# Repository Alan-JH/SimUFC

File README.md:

# SimUFC
UFC design for DCS, based on the F-18C Hornet

Display panels originally designed by [OpenHornet](https://github.com/jrsteensen/OpenHornet) and remixed to use .1" headers and multiplexed digits instead of multiplexed half digits.

Displays driven by Holtek HT1632Cs. Board is designed to take Cherry style key switches. I am using Kailh Box Jades, hence the SMD LEDs.

Main assembly is two large PCBs stacked, with the back PCB housing the LED drivers and microcontroller. It is designed to also take a shift register PCB of one of my older designs. It will be replaced later on.

Microcontroller is an STM32 Bluepill.

[![CC BY-NC-SA 4.0][cc-by-nc-sa-shield]][cc-by-nc-sa]

This work is licensed under a
[Creative Commons Attribution-NonCommercial-ShareAlike 4.0 International License][cc-by-nc-sa].

[![CC BY-NC-SA 4.0][cc-by-nc-sa-image]][cc-by-nc-sa]

[cc-by-nc-sa]: http://creativecommons.org/licenses/by-nc-sa/4.0/
[cc-by-nc-sa-image]: https://licensebuttons.net/l/by-nc-sa/4.0/88x31.png
[cc-by-nc-sa-shield]: https://img.shields.io/badge/License-CC%20BY--NC--SA%204.0-lightgrey.svg

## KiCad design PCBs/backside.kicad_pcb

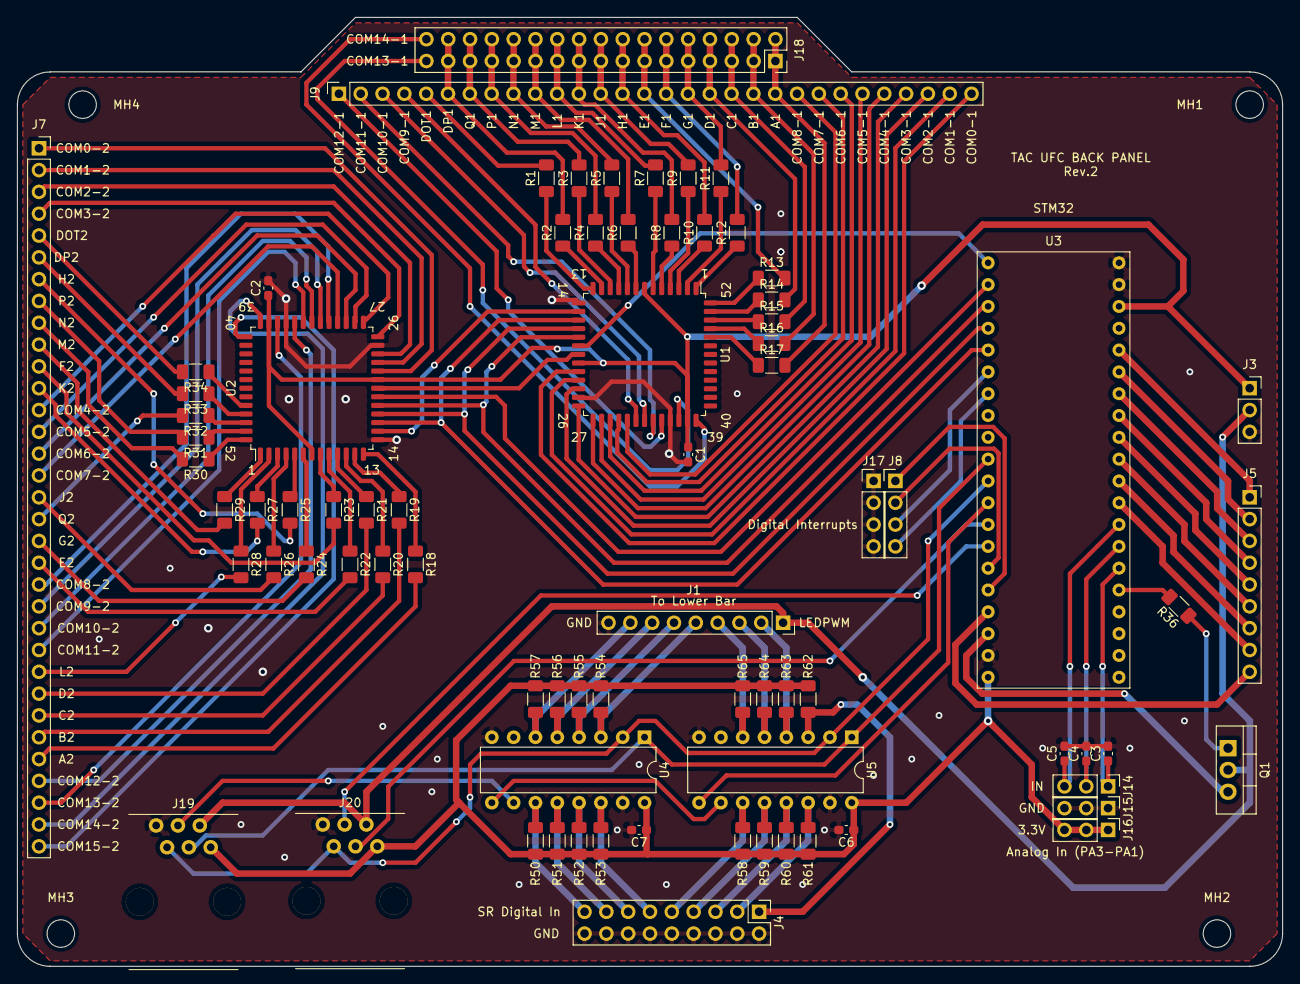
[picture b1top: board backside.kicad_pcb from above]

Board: 2 copper layers, 147.3 x 110.5 mm, 82 parts (0 on the bottom side), 151 nets.

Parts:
C1, C2, C3, C4, C5, C6, C7: .1uF; C_0603_1608Metric_Pad1.08x0.95mm_HandSolder
J1: 9Pin; PinSocket_1x09_P2.54mm_Vertical
J3: Power; PinSocket_1x03_P2.54mm_Vertical
J4: Conn_02x09_Odd_Even; PinHeader_2x09_P2.54mm_Vertical
J5: Matrix; PinSocket_1x09_P2.54mm_Vertical
J7: Driver output 2; PinSocket_1x33_P2.54mm_Vertical
J8, J17: Conn_01x04_Male; PinHeader_1x04_P2.54mm_Vertical
J9: Conn_01x30_Male; PinSocket_1x30_P2.54mm_Vertical
J14, J15, J16: Conn_01x03_Male; PinHeader_1x03_P2.54mm_Vertical
J18: Conn_02x17_Odd_Even; PinSocket_2x17_P2.54mm_Vertical
J19, J20: RJ12; SS-6466-NF
MH1, MH2, MH3, MH4: MountingHole_3.2mm_M3
Q1: IPP120P04P4L03; TO-220-3_Vertical
R1, R2, R3, R4, R5, R6, R7, R8, R9, R10, R11, R12, R13, R14, R15, R16, R17, R18, R19, R20, R21, R22, R23, R24, R25, R26, R27, R28, R29, R30, R31, R32, R33, R34: 510R; R_1206_3216Metric_Pad1.30x1.75mm_HandSolder
R36: 100R; R_1206_3216Metric_Pad1.30x1.75mm_HandSolder
R50, R51, R52, R53, R54, R55, R56, R57, R58, R59, R60, R61, R62, R63, R64, R65: 10K; R_1206_3216Metric_Pad1.30x1.75mm_HandSolder
U1, U2: HT1632C-52LQFP; LQFP-52_14x14mm_P1mm
U3: STM32F103C8T6; Bluepill
U4, U5: 74HC165; DIP-16_W7.62mm

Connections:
/3.3V: C1.1, C2.1, C6.1, C7.1, J3.1, J16.1, J16.2, J16.3, J19.6, J20.6, R50.2, R51.2, R52.2, R53.2, R54.2, R55.2, R56.2, R57.2, R58.2, R59.2, R60.2, R61.2, R62.2, R63.2, R64.2, R65.2, U1.7, U1.21, U1.38, U2.7, U2.21, U2.38, U3.47, U3.52, U4.16, U5.16
/5V: Q1.3, U3.50
/A1: J9.21, J18.1, J18.2, R17.2
/A2: J7.29, R18.2
/Analog1: C3.1, J14.1, U3.11
/Analog2: C4.1, J14.2, U3.12
/Analog3: C5.1, J14.3, U3.13
/B1: J9.20, J18.3, J18.4, R16.2
/B2: J7.28, R19.2
/C1: J9.19, J18.5, J18.6, R15.2
/C2: J7.27, R20.2
/COL1: J5.4, U3.18
/COL2: J5.3, U3.19
/COL3: J5.2, U3.21
/COL4: J5.1, U3.22
/COM0-1: J9.30, U1.22
/COM0-2: J7.1, U2.22
/COM1-1: J9.29, U1.23
/COM1-2: J7.2, U2.23
/COM2-1: J9.28, U1.24
/COM2-2: J7.3, U2.24
/COM3-1: J9.27, U1.26
/COM3-2: J7.4, U2.26
/COM4-1: J9.26, U1.27
/COM4-2: J7.13, U2.27
/COM5-1: J9.25, U1.28
/COM5-2: J7.14, U2.28
/COM6-1: J9.24, U1.29
/COM6-2: J7.15, U2.29
/COM7-1: J9.23, U1.30
/COM7-2: J7.16, U2.30
/COM8-1: J9.22, U1.31
/COM8-2: J7.21, U2.31
/COM9-1: J9.4, U1.32
/COM9-2: J7.22, U2.32
/COM10-1: J9.3, U1.33
/COM10-2: J7.23, U2.33
/COM11-1: J9.2, U1.34
/COM11-2: J7.24, U2.34
/COM12-1: J9.1, U1.35
/COM12-2: J7.30, U2.35
/COM13-1: J18.33, U1.37
/COM13-2: J7.31, U2.37
/COM14-1: J18.34, U1.39
/COM14-2: J7.32, U2.39
/COM15-2: J7.33, U2.40
/CS1: U1.19, U3.25
/CS2: U2.19, U3.26
/D1: J9.18, J18.7, J18.8, R14.2
/D2: J7.26, R21.2
/DATA: U1.16, U2.16, U3.29
/DIN1: J4.1, R62.1, U5.3
/DIN2: J4.3, R61.1, U5.14
/DIN3: J4.5, R60.1, U5.13
/DIN4: J4.7, R59.1, U5.12
/DIN5: J4.9, R58.1, U5.11
/DIN6: J4.11, R53.1, U4.14
/DIN7: J4.13, R52.1, U4.13
/DIN8: J4.15, R51.1, U4.12
/DIN9: J4.17, R50.1, U4.11
/DOT1: J9.5, R1.2
/DOT2: J7.5, R34.2
/DP1: J9.6, J18.31, J18.32, R2.2
/DP2: J7.6, R33.2
/DSIN: J19.3, U4.10
/DigInt1: J8.1, U3.45
/DigInt2: J8.2, U3.43
/DigInt3: J8.3, U3.30
/DigInt4: J8.4, U3.31
/E1: J9.15, J18.13, J18.14, R13.2
/E2: J7.20, R22.2
/F1: J9.16, J18.11, J18.12, R12.2
/F2: J7.11, R23.2
/G1: J9.17, J18.9, J18.10, R11.2
/G2: J7.19, R24.2
/GND: C1.2, C2.2, C3.2, C4.2, C5.2, C6.2, C7.2, J1.9, J3.3, J4.2, J4.4, J4.6, J4.8, J4.10, J4.12, J4.14, J4.16, J4.18, J15.1, J15.2, J15.3, J17.1, J17.2, J17.3, J17.4, J19.1, J20.1, U1.14, U1.25, U1.36, U2.14, U2.25, U2.36, U3.48, U3.49, U3.51, U4.8, U4.15, U5.8, U5.15
/H1: J9.14, J18.15, J18.16, R10.2
/H2: J7.7, R25.2
/J1: J9.13, J18.17, J18.18, R9.2
/J2: J7.17, R26.2
/K1: J9.12, J18.19, J18.20, R8.2
/K2: J7.12, R27.2
/L1: J9.11, J18.21, J18.22, R7.2
/L2: J7.25, R28.2
/LEDPWM: J1.1, J3.2, J19.5, J20.5, Q1.2
/M1: J9.10, J18.23, J18.24, R6.2
/M2: J7.10, R29.2
/N1: J9.9, J18.25, J18.26, R5.2
/N2: J7.9, R30.2
/OSC: U1.15, U2.15
/P1: J9.8, J18.27, J18.28, R4.2
/P2: J7.8, R31.2
/Q1: J9.7, J18.29, J18.30, R3.2
/Q2: J7.18, R32.2
/RD: U1.18, U2.18, U3.27
/ROW0: J5.5, U3.17
/ROW1: J5.6, U3.16
/ROW2: J5.7, U3.15
/ROW3: J5.8, U3.14
/ROW4: J5.9, U3.46
/SRCLK: J19.2, J20.2, U3.39, U4.2, U5.2
/SRCS: J19.4, U3.38, U4.1, U5.1
/SRCS2: J20.4, U3.41
/SRMISO: U3.40, U5.9
/SRMISO2: J20.3, U3.42
/SW18: J1.8, R57.1, U4.6
/SW19: J1.7, R56.1, U4.5
/SW20: J1.6, R55.1, U4.4
/SW21: J1.5, R54.1, U4.3
/SW22: J1.4, R65.1, U5.6
/SW23: J1.3, R64.1, U5.5
/SW24: J1.2, R63.1, U5.4
/SYNC: U1.20, U2.20
/WR: U1.17, U2.17, U3.28
unnamed: Q1.1, R36.1
unnamed: R1.1, U1.13
unnamed: R2.1, U1.12
unnamed: R3.1, U1.11
unnamed: R4.1, U1.10
unnamed: R5.1, U1.9
unnamed: R6.1, U1.8
unnamed: R7.1, U1.6
unnamed: R8.1, U1.5
unnamed: R9.1, U1.4
unnamed: R10.1, U1.3
unnamed: R11.1, U1.2
unnamed: R12.1, U1.1
unnamed: R13.1, U1.52
unnamed: R14.1, U1.51
unnamed: R15.1, U1.50
unnamed: R16.1, U1.49
unnamed: R17.1, U1.48
unnamed: R18.1, U2.13
unnamed: R19.1, U2.12
unnamed: R20.1, U2.11
unnamed: R21.1, U2.10
unnamed: R22.1, U2.9
unnamed: R23.1, U2.8
unnamed: R24.1, U2.6
unnamed: R25.1, U2.5
unnamed: R26.1, U2.4
unnamed: R27.1, U2.3
unnamed: R28.1, U2.2
unnamed: R29.1, U2.1
unnamed: R30.1, U2.52
unnamed: R31.1, U2.51
unnamed: R32.1, U2.50
unnamed: R33.1, U2.49
unnamed: R34.1, U2.48
unnamed: R36.2, U3.10
unnamed: U4.9, U5.10

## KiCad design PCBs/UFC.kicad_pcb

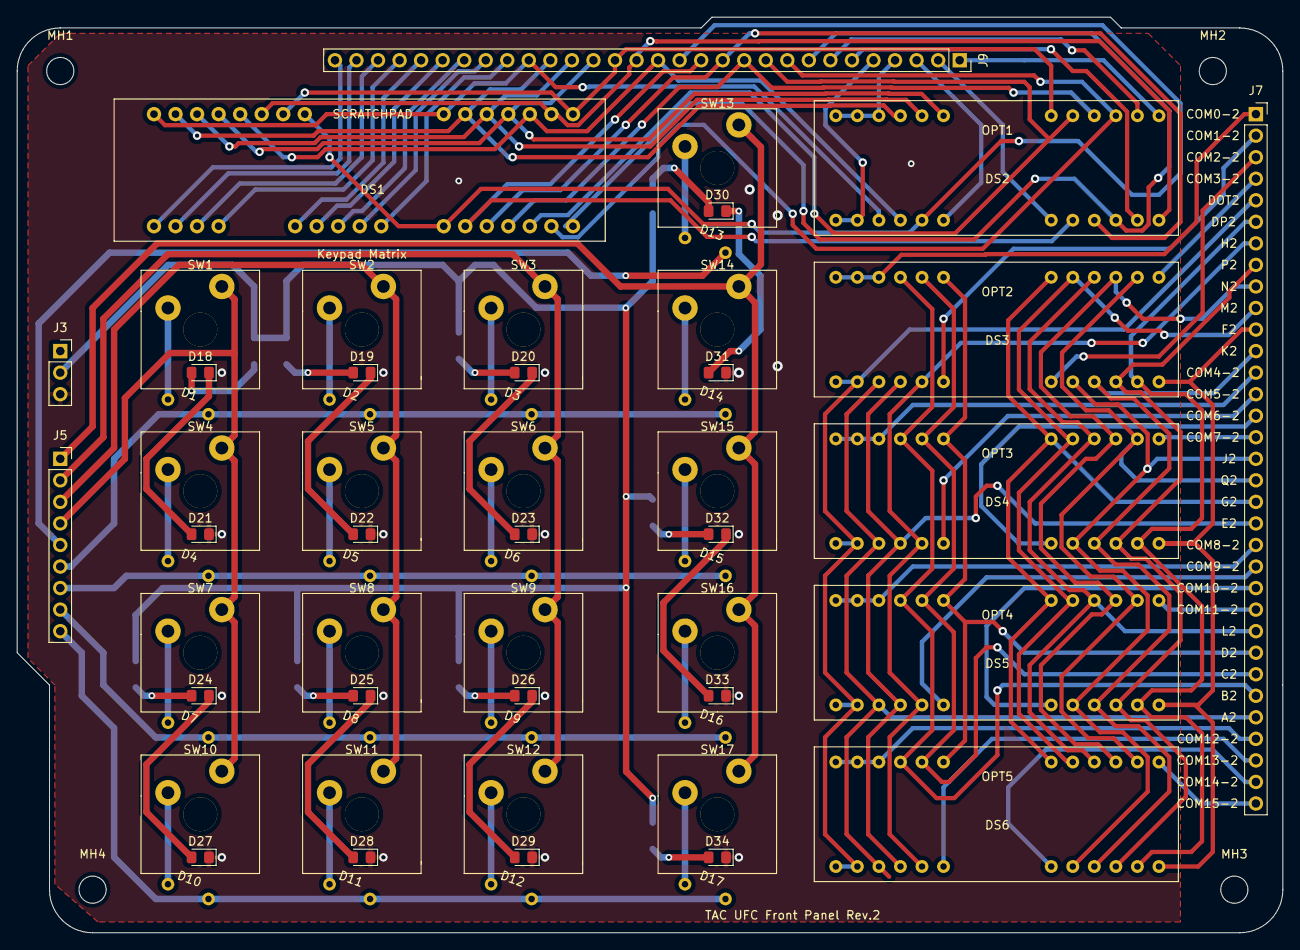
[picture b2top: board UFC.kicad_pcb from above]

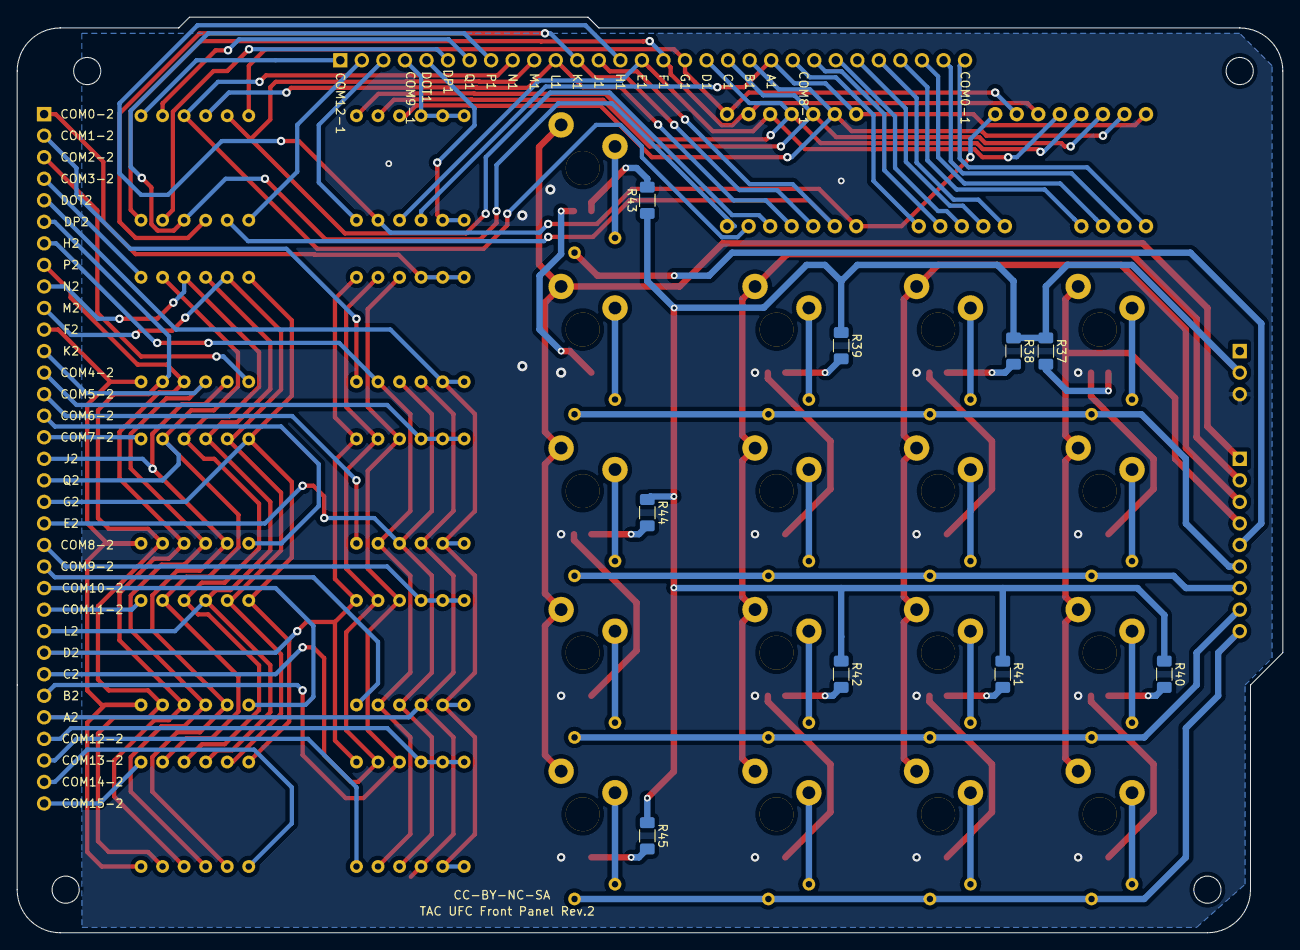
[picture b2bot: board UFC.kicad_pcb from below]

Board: 2 copper layers, 149.2 x 108.0 mm, 74 parts (9 on the bottom side), 108 nets.

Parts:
D1, D2, D3, D4, D5, D6, D7, D8, D9, D10, D11, D12, D13, D14, D15, D16, D17: D; 1N4148
D18, D19, D20, D21, D22, D23, D24, D25, D26, D27, D28, D29, D30, D31, D32, D33, D34: LED; LED_0805_2012Metric_Pad1.15x1.40mm_HandSolder
DS1: Scratchpad
DS2, DS3, DS4, DS5, DS6: CustomOptPanel; OPTDisplay
J3: Power; PinSocket_1x03_P2.54mm_Vertical
J5: Matrix; PinSocket_1x09_P2.54mm_Vertical
J7: Driver output 2; PinSocket_1x33_P2.54mm_Vertical
J9: Conn_01x30_Male; PinSocket_1x30_P2.54mm_Vertical
MH1, MH2, MH3, MH4: MountingHole_3.2mm_M3
R37, R38, R39, R40, R41, R42, R43, R44: 100R; R_1206_3216Metric_Pad1.30x1.75mm_HandSolder
R45: 300R; R_1206_3216Metric_Pad1.30x1.75mm_HandSolder
SW1, SW2, SW3, SW4, SW5, SW6, SW7, SW8, SW9, SW10, SW11, SW12, SW13, SW14, SW15, SW16, SW17: KeySW; KailhSW

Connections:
/A1: DS1.1, DS1.9, DS2.15, J9.21
/A2: DS3.15, DS4.15, DS5.15, DS6.15, J7.29
/B1: DS1.2, DS1.10, DS2.4, J9.20
/B2: DS3.4, DS4.4, DS5.4, DS6.4, J7.28
/C1: DS1.3, DS1.11, DS2.5, J9.19
/C2: DS3.5, DS4.5, DS5.5, DS6.5, J7.27
/COL1: J5.4, SW1.2, SW4.2, SW7.2, SW10.2
/COL2: J5.3, SW2.2, SW5.2, SW8.2, SW11.2
/COL3: J5.2, SW3.2, SW6.2, SW9.2, SW12.2
/COL4: J5.1, SW13.2, SW14.2, SW15.2, SW16.2, SW17.2
/COM0-1: DS1.16, J9.30
/COM0-2: DS3.1, DS3.2, DS3.3, J7.1
/COM1-1: DS1.17, J9.29
/COM1-2: DS3.18, J7.2
/COM2-1: DS1.18, J9.28
/COM2-2: DS3.19, J7.3
/COM3-1: DS1.19, J9.27
/COM3-2: DS3.12, J7.4
/COM4-1: DS1.20, J9.26
/COM4-2: DS4.1, DS4.2, DS4.3, J7.13
/COM5-1: DS1.21, J9.25
/COM5-2: DS4.18, J7.14
/COM6-1: DS1.22, J9.24
/COM6-2: DS4.19, J7.15
/COM7-1: DS1.23, J9.23
/COM7-2: DS4.12, J7.16
/COM8-1: DS1.24, J9.22
/COM8-2: DS5.1, DS5.2, DS5.3, J7.21
/COM9-1: DS2.1, DS2.2, DS2.3, J9.4
/COM9-2: DS5.18, J7.22
/COM10-1: DS2.18, J9.3
/COM10-2: DS5.19, J7.23
/COM11-1: DS2.19, J9.2
/COM11-2: DS5.12, J7.24
/COM12-1: DS2.12, J9.1
/COM12-2: DS6.1, DS6.2, DS6.3, J7.30
/COM13-2: DS6.18, J7.31
/COM14-2: DS6.19, J7.32
/COM15-2: DS6.12, J7.33
/D1: DS1.4, DS1.12, DS2.6, J9.18
/D2: DS3.6, DS4.6, DS5.6, DS6.6, J7.26
/DOT1: DS2.13, DS2.14, J9.5
/DOT2: DS3.13, DS3.14, DS4.13, DS4.14, DS5.13, DS5.14, DS6.13, DS6.14, J7.5
/DP1: DS2.23, J9.6
/DP2: DS3.23, DS4.23, DS5.23, DS6.23, J7.6
/E1: DS1.5, DS1.13, DS2.16, J9.15
/E2: DS3.16, DS4.16, DS5.16, DS6.16, J7.20
/F1: DS1.6, DS1.14, DS2.24, J9.16
/F2: DS3.24, DS4.24, DS5.24, DS6.24, J7.11
/G1: DS1.7, DS1.15, DS2.7, J9.17
/G2: DS3.7, DS4.7, DS5.7, DS6.7, J7.19
/GND: D21.1, D22.1, D23.1, D27.1, D28.1, D29.1, D31.1, D33.1, D34.1, J3.3
/H1: DS1.8, DS1.25, DS2.17, J9.14
/H2: DS3.17, DS4.17, DS5.17, DS6.17, J7.7
/J1: DS1.26, DS2.20, J9.13
/J2: DS3.20, DS4.20, DS5.20, DS6.20, J7.17
/K1: DS1.27, DS2.21, J9.12
/K2: DS3.21, DS4.21, DS5.21, DS6.21, J7.12
/L1: DS1.28, DS2.9, J9.11
/L2: DS3.9, DS4.9, DS5.9, DS6.9, J7.25
/LEDPWM: J3.2, R37.1, R38.1, R39.1, R40.1, R41.1, R42.1, R43.1, R44.1, R45.1
/M1: DS1.29, DS2.8, J9.10
/M2: DS3.8, DS4.8, DS5.8, DS6.8, J7.10
/N1: DS1.30, DS2.10, J9.9
/N2: DS3.10, DS4.10, DS5.10, DS6.10, J7.9
/P1: DS1.31, DS2.22, J9.8
/P2: DS3.22, DS4.22, DS5.22, DS6.22, J7.8
/Q1: DS2.11, J9.7
/Q2: DS3.11, DS4.11, DS5.11, DS6.11, J7.18
/ROW0: D13.1, J5.5
/ROW1: D1.1, D2.1, D3.1, D14.1, J5.6
/ROW2: D4.1, D5.1, D6.1, D15.1, J5.7
/ROW3: D7.1, D8.1, D9.1, D16.1, J5.8
/ROW4: D10.1, D11.1, D12.1, D17.1, J5.9
unnamed: D1.2, SW1.1
unnamed: D2.2, SW2.1
unnamed: D3.2, SW3.1
unnamed: D4.2, SW4.1
unnamed: D5.2, SW5.1
unnamed: D6.2, SW6.1
unnamed: D7.2, SW7.1
unnamed: D8.2, SW8.1
unnamed: D9.2, SW9.1
unnamed: D10.2, SW10.1
unnamed: D11.2, SW11.1
unnamed: D12.2, SW12.1
unnamed: D13.2, SW13.1
unnamed: D14.2, SW14.1
unnamed: D15.2, SW15.1
unnamed: D16.2, SW16.1
unnamed: D17.2, SW17.1
unnamed: D18.1, D21.2
unnamed: D18.2, R37.2
unnamed: D19.1, D22.2
unnamed: D19.2, R38.2
unnamed: D20.1, D23.2
unnamed: D20.2, R39.2
unnamed: D24.1, D27.2
unnamed: D24.2, R40.2
unnamed: D25.1, D28.2
unnamed: D25.2, R41.2
unnamed: D26.1, D29.2
unnamed: D26.2, R42.2
unnamed: D30.1, D31.2
unnamed: D30.2, R43.2
unnamed: D32.1, D33.2
unnamed: D32.2, R44.2
unnamed: D34.2, R45.2

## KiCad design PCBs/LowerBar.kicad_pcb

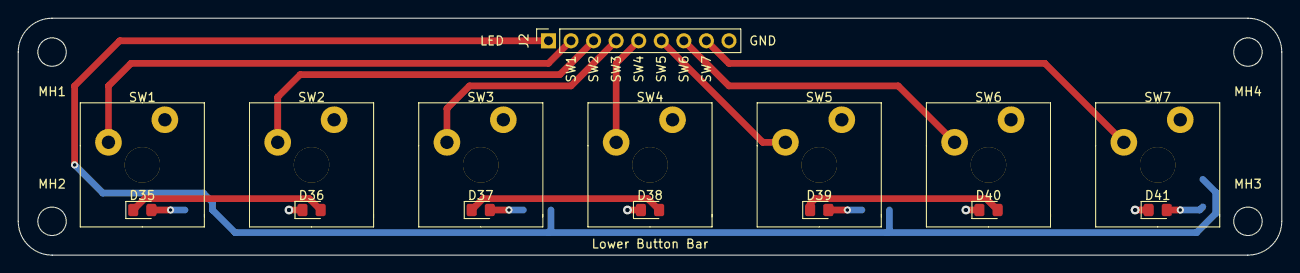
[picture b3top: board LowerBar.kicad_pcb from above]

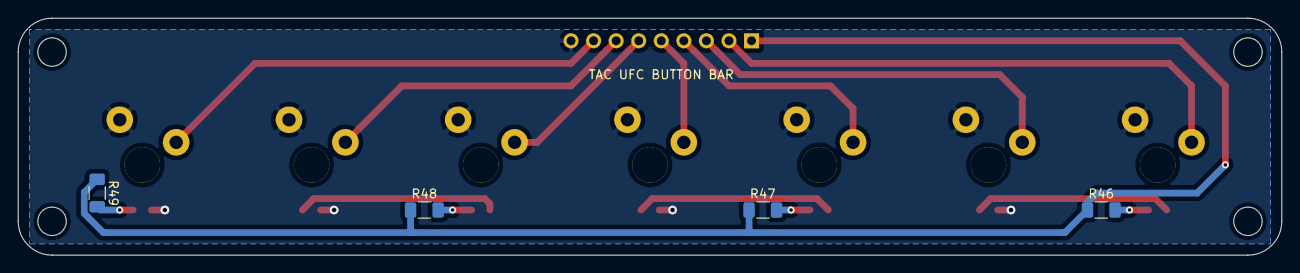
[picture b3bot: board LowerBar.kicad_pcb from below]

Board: 2 copper layers, 142.2 x 26.7 mm, 23 parts (4 on the bottom side), 16 nets.

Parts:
D35, D36, D37, D38, D39, D40, D41: LED; LED_0805_2012Metric_Pad1.15x1.40mm_HandSolder
J2: 9pin; PinSocket_1x09_P2.54mm_Vertical
MH1, MH2, MH3, MH4: M3; MountingHole_3.2mm_M3
R46, R47, R48: 100R; R_1206_3216Metric_Pad1.30x1.75mm_HandSolder
R49: 300R; R_1206_3216Metric_Pad1.30x1.75mm_HandSolder
SW1, SW2, SW3, SW4, SW5, SW6, SW7: KeySW; KailhSW

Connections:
/GND: D36.1, D38.1, D40.1, D41.1, J2.9, SW1.2, SW2.2, SW3.2, SW4.2, SW5.2, SW6.2, SW7.2
/LED: J2.1, R46.1, R47.1, R48.1, R49.1
/SW18: J2.2, SW1.1
/SW19: J2.3, SW2.1
/SW20: J2.4, SW3.1
/SW21: J2.5, SW4.1
/SW22: J2.6, SW5.1
/SW23: J2.7, SW6.1
/SW24: J2.8, SW7.1
unnamed: D35.1, D36.2
unnamed: D35.2, R46.2
unnamed: D37.1, D38.2
unnamed: D37.2, R47.2
unnamed: D39.1, D40.2
unnamed: D39.2, R48.2
unnamed: D41.2, R49.2

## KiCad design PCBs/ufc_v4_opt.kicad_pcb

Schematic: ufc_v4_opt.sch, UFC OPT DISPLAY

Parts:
D1, D2, D3, D4, D5, D6, D7, D8, D9, D10, D11, D12, D13, D14, D15, D16, D17, D18, D19, D20, D21, D22, D23, D24, D25, D26, D27, D28, D29, D30, D31, D32, D33, D34, D35, D36, D37, D38, D39, D40, D41, D42, D43, D44, D45, D46, D47, D48, D49, D50, D51, D52, D53, D54, D55, D56, D57, D58, D59, D60, D61, D62, D63, D64, D65, D66: LED; LED_0402_1005Metric; LCSC C130723
J1, J2, J3, J4: Conn_01x06_Male; PinHeader_1x06_P2.54mm_Vertical

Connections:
/DIG0: D1.1 (K), D2.1 (K), D3.1 (K), D4.1 (K), D5.1 (K), D6.1 (K), D7.1 (K), D8.1 (K), D9.1 (K), D10.1 (K), D11.1 (K), D12.1 (K), D13.1 (K), D14.1 (K), D15.1 (K), D16.1 (K), J1.3
/DIG1: D17.1 (K), D18.1 (K), D19.1 (K), D20.1 (K), D21.1 (K), D22.1 (K), D23.1 (K), D24.1 (K), D25.1 (K), D26.1 (K), D27.1 (K), D28.1 (K), D29.1 (K), D30.1 (K), D31.1 (K), D32.1 (K), J3.6
/DIG2: D33.1 (K), D34.1 (K), D35.1 (K), D36.1 (K), D37.1 (K), D38.1 (K), D39.1 (K), D40.1 (K), D41.1 (K), D42.1 (K), D43.1 (K), D44.1 (K), D45.1 (K), D46.1 (K), D47.1 (K), D48.1 (K), J4.1
/DIG3: D49.1 (K), D50.1 (K), D51.1 (K), D52.1 (K), D53.1 (K), D54.1 (K), D55.1 (K), D56.1 (K), D57.1 (K), D58.1 (K), D59.1 (K), D60.1 (K), D61.1 (K), D62.1 (K), D63.1 (K), D64.1 (K), J2.6
/DOT1+: D65.2 (A), J3.1
/DOT1-: D65.1 (K), J1.1
/DOT2+: D66.2 (A), J3.2
/DOT2-: D66.1 (K), J1.2
/SEGA: D7.2 (A), D23.2 (A), D39.2 (A), D55.2 (A), J3.3
/SEGB: D8.2 (A), D24.2 (A), D40.2 (A), D56.2 (A), J1.4
/SEGC: D1.2 (A), D17.2 (A), D33.2 (A), D49.2 (A), J1.5
/SEGD: D3.2 (A), D19.2 (A), D35.2 (A), D51.2 (A), J1.6
/SEGDP: D2.2 (A), D18.2 (A), D34.2 (A), D50.2 (A), J4.5
/SEGE: D6.2 (A), D22.2 (A), D38.2 (A), D54.2 (A), J3.4
/SEGF: D5.2 (A), D21.2 (A), D37.2 (A), D53.2 (A), J4.6
/SEGG: D4.2 (A), D20.2 (A), D36.2 (A), D52.2 (A), J2.1
/SEGH: D9.2 (A), D25.2 (A), D41.2 (A), D57.2 (A), J3.5
/SEGJ: D14.2 (A), D30.2 (A), D46.2 (A), D62.2 (A), J4.2
/SEGK: D13.2 (A), D29.2 (A), D45.2 (A), D61.2 (A), J4.3
/SEGL: D12.2 (A), D28.2 (A), D44.2 (A), D60.2 (A), J2.3
/SEGM: D11.2 (A), D27.2 (A), D43.2 (A), D59.2 (A), J2.2
/SEGN: D10.2 (A), D26.2 (A), D42.2 (A), D58.2 (A), J2.4
/SEGP: D16.2 (A), D32.2 (A), D48.2 (A), D64.2 (A), J4.4
/SEGQ: D15.2 (A), D31.2 (A), D47.2 (A), D63.2 (A), J2.5

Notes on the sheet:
to make software simpler each display digit was divided into halves. This distribution ensures that MAX digit 0 +1 become a single digit with identical representation as MAX digit 2 + 3
half digit Right
Half digit Left

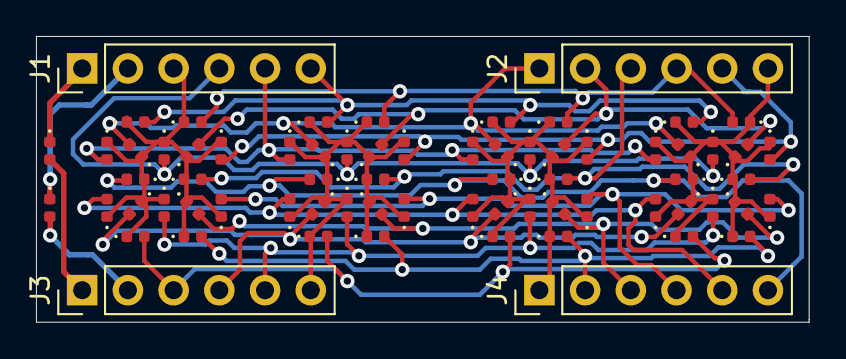
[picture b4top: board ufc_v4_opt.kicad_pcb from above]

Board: 2 copper layers, 42.9 x 15.9 mm, 70 parts (0 on the bottom side), 24 nets.

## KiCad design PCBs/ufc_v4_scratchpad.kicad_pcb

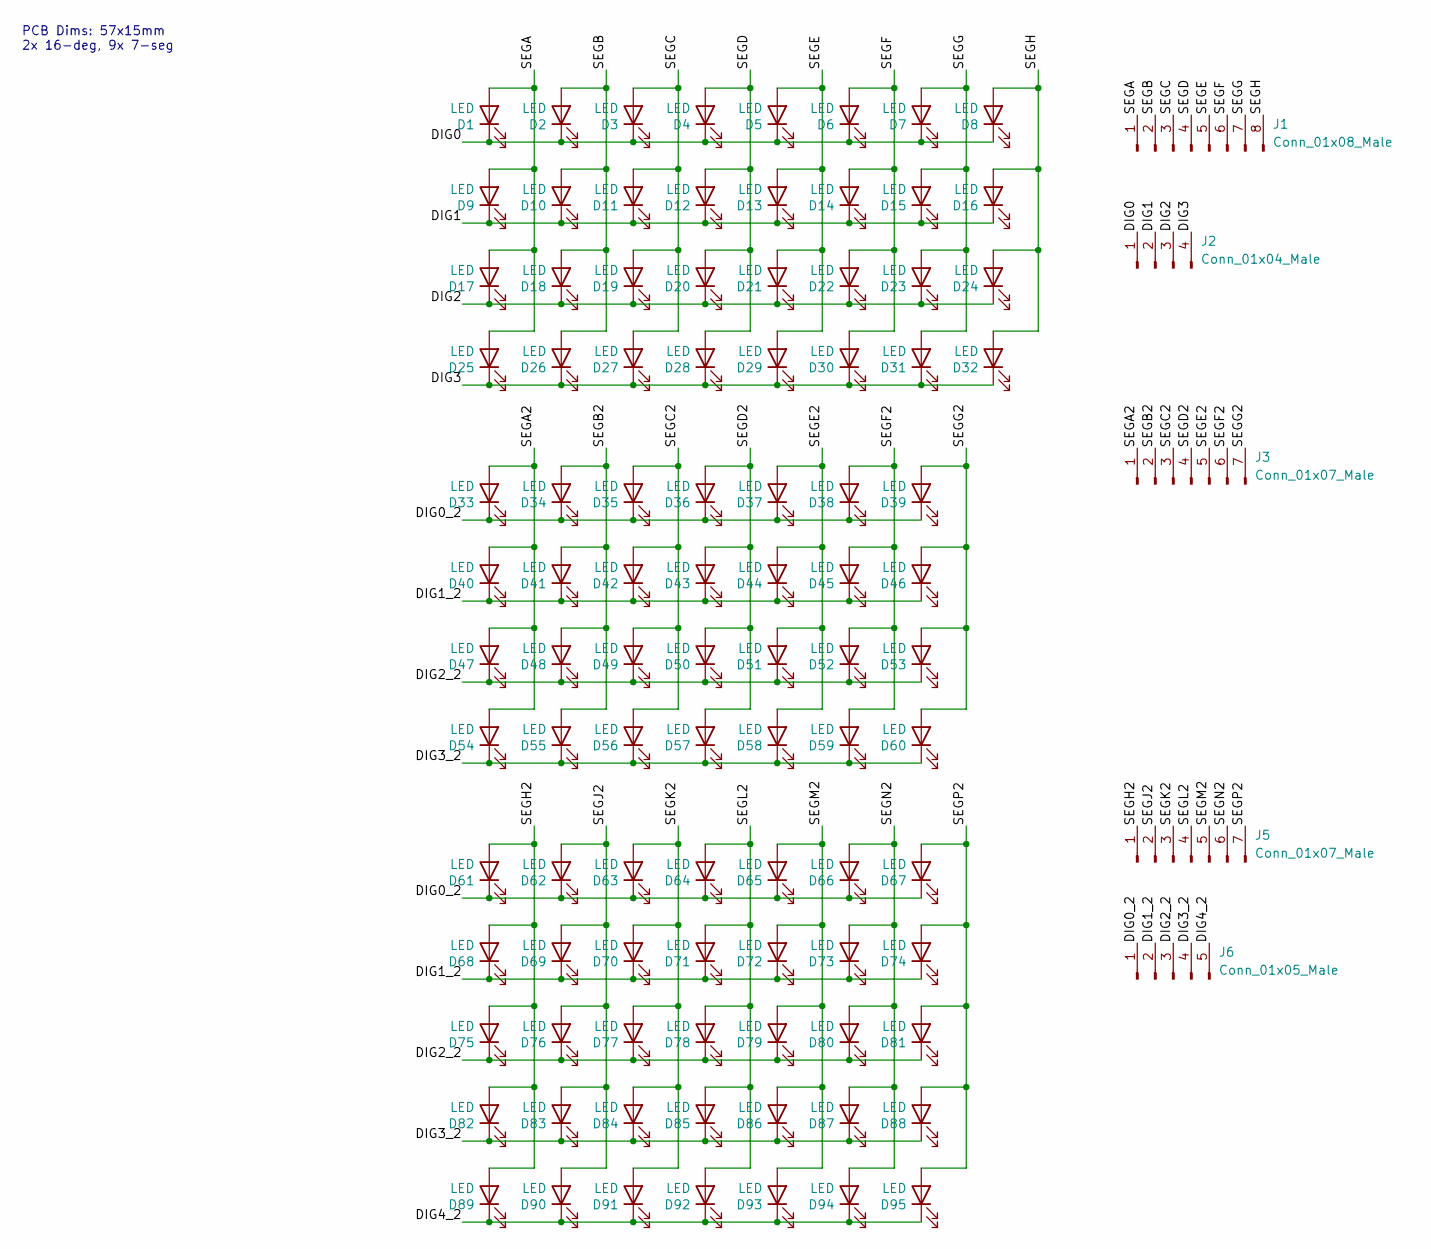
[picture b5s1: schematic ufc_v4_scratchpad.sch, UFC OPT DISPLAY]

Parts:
D1, D2, D3, D4, D5, D6, D7, D8, D9, D10, D11, D12, D13, D14, D15, D16, D17, D18, D19, D20, D21, D22, D23, D24, D25, D26, D27, D28, D29, D30, D31, D32, D33, D34, D35, D36, D37, D38, D39, D40, D41, D42, D43, D44, D45, D46, D47, D48, D49, D50, D51, D52, D53, D54, D55, D56, D57, D58, D59, D60, D61, D62, D63, D64, D65, D66, D67, D68, D69, D70, D71, D72, D73, D74, D75, D76, D77, D78, D79, D80, D81, D82, D83, D84, D85, D86, D87, D88, D89, D90, D91, D92, D93, D94, D95: LED; LED_0402_1005Metric; LCSC C130723
J1: Conn_01x08_Male; PinHeader_1x08_P2.54mm_Vertical
J2: Conn_01x04_Male; PinHeader_1x04_P2.54mm_Vertical
J3, J5: Conn_01x07_Male; PinHeader_1x07_P2.54mm_Vertical
J6: Conn_01x05_Male; PinHeader_1x05_P2.54mm_Vertical

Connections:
/DIG0: D1.1 (K), D2.1 (K), D3.1 (K), D4.1 (K), D5.1 (K), D6.1 (K), D7.1 (K), D8.1 (K), J2.1
/DIG0_2: D33.1 (K), D34.1 (K), D35.1 (K), D36.1 (K), D37.1 (K), D38.1 (K), D39.1 (K), D61.1 (K), D62.1 (K), D63.1 (K), D64.1 (K), D65.1 (K), D66.1 (K), D67.1 (K), J6.1
/DIG1: D9.1 (K), D10.1 (K), D11.1 (K), D12.1 (K), D13.1 (K), D14.1 (K), D15.1 (K), D16.1 (K), J2.2
/DIG1_2: D40.1 (K), D41.1 (K), D42.1 (K), D43.1 (K), D44.1 (K), D45.1 (K), D46.1 (K), D68.1 (K), D69.1 (K), D70.1 (K), D71.1 (K), D72.1 (K), D73.1 (K), D74.1 (K), J6.2
/DIG2: D17.1 (K), D18.1 (K), D19.1 (K), D20.1 (K), D21.1 (K), D22.1 (K), D23.1 (K), D24.1 (K), J2.3
/DIG2_2: D47.1 (K), D48.1 (K), D49.1 (K), D50.1 (K), D51.1 (K), D52.1 (K), D53.1 (K), D75.1 (K), D76.1 (K), D77.1 (K), D78.1 (K), D79.1 (K), D80.1 (K), D81.1 (K), J6.3
/DIG3: D25.1 (K), D26.1 (K), D27.1 (K), D28.1 (K), D29.1 (K), D30.1 (K), D31.1 (K), D32.1 (K), J2.4
/DIG3_2: D54.1 (K), D55.1 (K), D56.1 (K), D57.1 (K), D58.1 (K), D59.1 (K), D60.1 (K), D82.1 (K), D83.1 (K), D84.1 (K), D85.1 (K), D86.1 (K), D87.1 (K), D88.1 (K), J6.4
/DIG4_2: D89.1 (K), D90.1 (K), D91.1 (K), D92.1 (K), D93.1 (K), D94.1 (K), D95.1 (K), J6.5
/SEGA: D1.2 (A), D9.2 (A), D17.2 (A), D25.2 (A), J1.1
/SEGA2: D33.2 (A), D40.2 (A), D47.2 (A), D54.2 (A), J3.1
/SEGB: D2.2 (A), D10.2 (A), D18.2 (A), D26.2 (A), J1.2
/SEGB2: D34.2 (A), D41.2 (A), D48.2 (A), D55.2 (A), J3.2
/SEGC: D3.2 (A), D11.2 (A), D19.2 (A), D27.2 (A), J1.3
/SEGC2: D35.2 (A), D42.2 (A), D49.2 (A), D56.2 (A), J3.3
/SEGD: D4.2 (A), D12.2 (A), D20.2 (A), D28.2 (A), J1.4
/SEGD2: D36.2 (A), D43.2 (A), D50.2 (A), D57.2 (A), J3.4
/SEGE: D5.2 (A), D13.2 (A), D21.2 (A), D29.2 (A), J1.5
/SEGE2: D37.2 (A), D44.2 (A), D51.2 (A), D58.2 (A), J3.5
/SEGF: D6.2 (A), D14.2 (A), D22.2 (A), D30.2 (A), J1.6
/SEGF2: D38.2 (A), D45.2 (A), D52.2 (A), D59.2 (A), J3.6
/SEGG: D7.2 (A), D15.2 (A), D23.2 (A), D31.2 (A), J1.7
/SEGG2: D39.2 (A), D46.2 (A), D53.2 (A), D60.2 (A), J3.7
/SEGH: D8.2 (A), D16.2 (A), D24.2 (A), D32.2 (A), J1.8
/SEGH2: D61.2 (A), D68.2 (A), D75.2 (A), D82.2 (A), D89.2 (A), J5.1
/SEGJ2: D62.2 (A), D69.2 (A), D76.2 (A), D83.2 (A), D90.2 (A), J5.2
/SEGK2: D63.2 (A), D70.2 (A), D77.2 (A), D84.2 (A), D91.2 (A), J5.3
/SEGL2: D64.2 (A), D71.2 (A), D78.2 (A), D85.2 (A), D92.2 (A), J5.4
/SEGM2: D65.2 (A), D72.2 (A), D79.2 (A), D86.2 (A), D93.2 (A), J5.5
/SEGN2: D66.2 (A), D73.2 (A), D80.2 (A), D87.2 (A), D94.2 (A), J5.6
/SEGP2: D67.2 (A), D74.2 (A), D81.2 (A), D88.2 (A), D95.2 (A), J5.7

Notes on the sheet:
PCB Dims: 57x15mm 2x 16-deg, 9x 7-seg

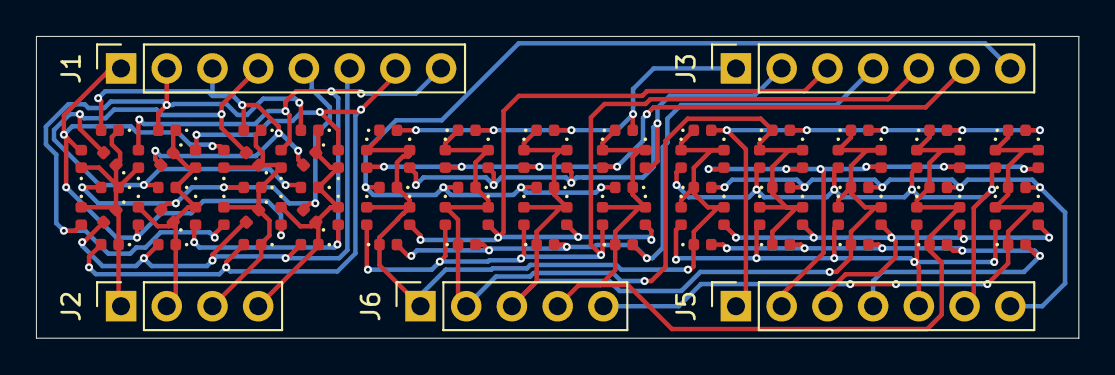
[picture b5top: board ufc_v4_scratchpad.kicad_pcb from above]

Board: 2 copper layers, 57.9 x 16.8 mm, 100 parts (0 on the bottom side), 31 nets.

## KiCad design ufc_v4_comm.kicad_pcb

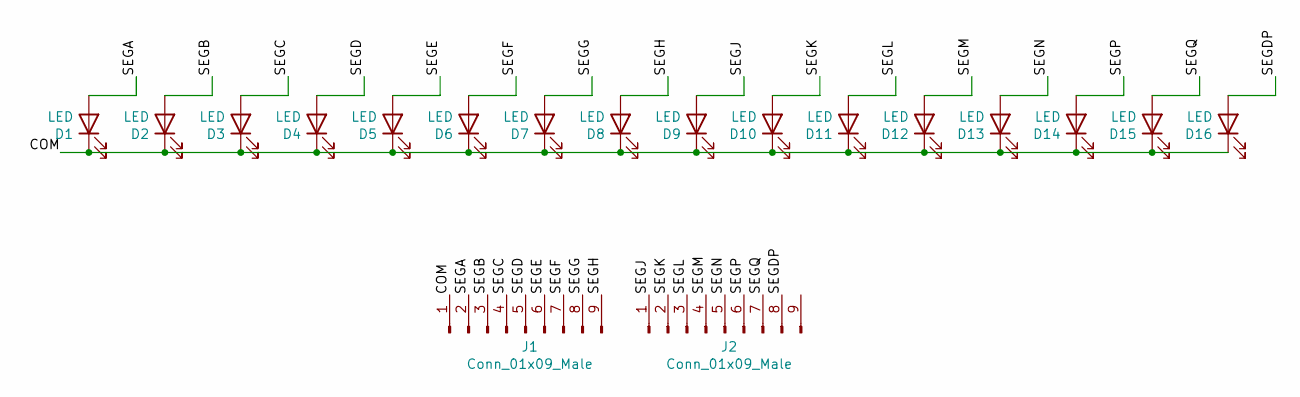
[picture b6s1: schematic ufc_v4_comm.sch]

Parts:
D1, D2, D3, D4, D5, D6, D7, D8, D9, D10, D11, D12, D13, D14, D15, D16: LED; LED_0402_1005Metric; LCSC C130723
J1, J2: Conn_01x09_Male; PinSocket_1x09_P2.54mm_Vertical

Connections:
/COM: D1.1 (K), D2.1 (K), D3.1 (K), D4.1 (K), D5.1 (K), D6.1 (K), D7.1 (K), D8.1 (K), D9.1 (K), D10.1 (K), D11.1 (K), D12.1 (K), D13.1 (K), D14.1 (K), D15.1 (K), D16.1 (K), J1.1
/SEGA: D1.2 (A), J1.2
/SEGB: D2.2 (A), J1.3
/SEGC: D3.2 (A), J1.4
/SEGD: D4.2 (A), J1.5
/SEGDP: D16.2 (A), J2.8
/SEGE: D5.2 (A), J1.6
/SEGF: D6.2 (A), J1.7
/SEGG: D7.2 (A), J1.8
/SEGH: D8.2 (A), J1.9
/SEGJ: D9.2 (A), J2.1
/SEGK: D10.2 (A), J2.2
/SEGL: D11.2 (A), J2.3
/SEGM: D12.2 (A), J2.4
/SEGN: D13.2 (A), J2.5
/SEGP: D14.2 (A), J2.6
/SEGQ: D15.2 (A), J2.7

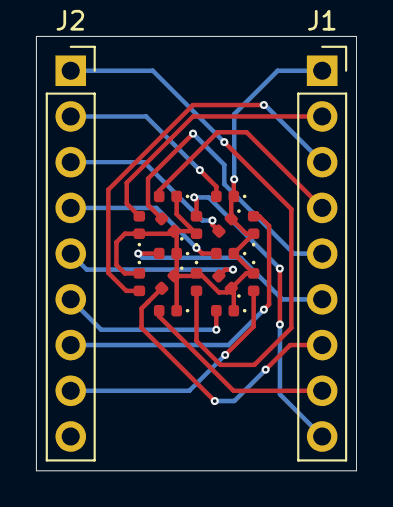
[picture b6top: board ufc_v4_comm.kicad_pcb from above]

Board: 2 copper layers, 17.8 x 24.1 mm, 18 parts (0 on the bottom side), 17 nets.

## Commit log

2021-05-09 WIP Kicad project
2021-05-10 Rerouted scratchpad and added to main schematic
    Rerouted the scratchpad traces so that it has only 9 common pins, and two sets of anodes
    A-H and A-P for 16 segment, where each common goes to half a 16 seg digit, and 7 segments respectively, where each common goes to two 7 seg digits. I plan to tie the first set of A-H together with th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
    Also replaced the 1mm pitch headers with 2.54mm headers
    Added a symbol to the library and added it to the main UFC schematic.
2021-05-10 Created scratchpad footprint
    Created a footprint for the scratchpad pins, and updated the layout
2021-05-12 Split up board, started routing traces
    Moved the LED drivers and the STM32 board off of the main board and onto a daughterboard to fit a reasonable space. Second board will go behind the first, connected with .1" headers.
    Additionally, traces on the bottom four (second LED driver) OPT displays are routed.
    Redid the OPT buttons to be included in the keypad matrix, to save pins.
    Removed the shift register pins and wired it all directly to the STM32, to save space
2021-05-13 Finished routing, updated comm channel displays
    Decided to use (and again modify) open hornet's com channel indicators. Finished routing traces and adding ground planes on the main board, though it may be a little sloppy. Began work on the back si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
2021-05-14 Routed back side board
    Routed the LED drivers, pin headers, shift registers, etc. that are on the back side. ECAD is close to done, and I will start on the MCAD at this point.
    -Decided to avoid routing anodes and common cathodes to each of the comm channel displays, as that would probably have required at least an extra layer, instead I added a header to plug crimped wires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
    -Some of the headers are two single width pin headers put side by side, meaning their courtyards overlap. I may redo this to use one footprint for both in the future.
    -Still undecided on a couple part values
2021-05-14 Updated silkscreen, fixed minor issues
    Updated silkscreen to show pin designations, and fixed an issue with ground plane
2021-05-14 Revert "Updated silkscreen, fixed minor issues"
    This reverts commit 7f968d800cd681b23a83898d0d52e0d98e75c2f4.
2021-05-14 Updated silkscreen, fixed minor issues
    Updated silkscreen to include pin designations, and fixed minor issue with ground plane
2021-05-15 Removed comm displays from PCB
    Since they will be connected with wires anyways it didn't make sense to keep them on.
2021-05-15 Added folders via local upload
    Folders include updated panelized files, footprint library, gerbers, and display layers.
2021-05-16 Added more space for connector on comm display
2021-05-16 Started MCAD
2021-05-18 Mostly finished UFC CAD
2021-05-30 Updated PCBs, cleaned up files
    No commit for a while; a lot has happened in the mean time. JLC refused my order for the display layers, so I settled for just the dot layer. The gerbers for the rest are deleted, but the kicad files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
    I also received the main PCBs from JLC, and edited a couple small details.
2021-05-30 Updated MCAD
    UFC CAD is finished, and now I just need to test print. Added STEP file for display layers 2-3, to be printed in resin or a <=0.2mm FDM nozzle.
    Laser cutting is an option but expensive
2021-06-08 STL Export
2021-06-08 Started Firmware
    Firmware is just DCS-BIOS display code, for now. HID functions will be added soon.
2021-06-10 Update MCAD screws
    Test printed top and face parts. Face part was missing screw holes, and counterbore for top part's M4 screws was not wide enough.
2021-06-10 Face spacer
    Split face and spacing pegs to PCB for ease of printing
2021-06-11 Fixed design error
    Untested as of now.
    Removed direct connection from PWM out to LEDs, as the PWM pins on the bluepill can't provide enough current. Added P channel mosfet, and individual resistors per parallel LED. For now, the single re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
2021-06-11 Draft BOM
    Only has electronics components for now.
2021-06-13 Added USB HID features
    Added USB HID library, added functions to read matrix and shift registers, and updated one of the characters in the CharacterMap file. DCS-BIOS library needs to be modified to call CompositeSerial in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
2021-06-13 Modification to DcsBios lib
2021-06-14 Updated channel knob dimensions
    Reduced the size of the hole for the channel selector from 9mm to 7mm, and added a hole for the indexer.
2021-06-14 Major revision to backside PCB
    Re-arranged pin assignments on the bluepill; sacrificed 4 Analog inputs for 2 more digital interrupts, and 2 more SPI CS pins.
    Added two RJ12 connectors so that the board can be connected to other devices that use just shift registers, such as MFDs
    Replaced footprint for 3x shift register sub-assembly PCB with 2 DIP16 74hc165s, and pullups and bypass caps.
    Re-arranged and replaced 0.1" headers as appropriate.
    Removed R35 and its bypass jumper, connecting LEDPWM directly to the MOSFET drain.
2021-06-21 Corrected extra shift register pins
    Replaced two latch pins with one latch and one data to one port, and made the other port daisy chained after the two shift registers on the board
2021-07-18 Updated Keycaps
    Made the keycaps hollow to try to make the backlighting more visible. Updated the dimensions on M3 nut inserts; they were too small before
